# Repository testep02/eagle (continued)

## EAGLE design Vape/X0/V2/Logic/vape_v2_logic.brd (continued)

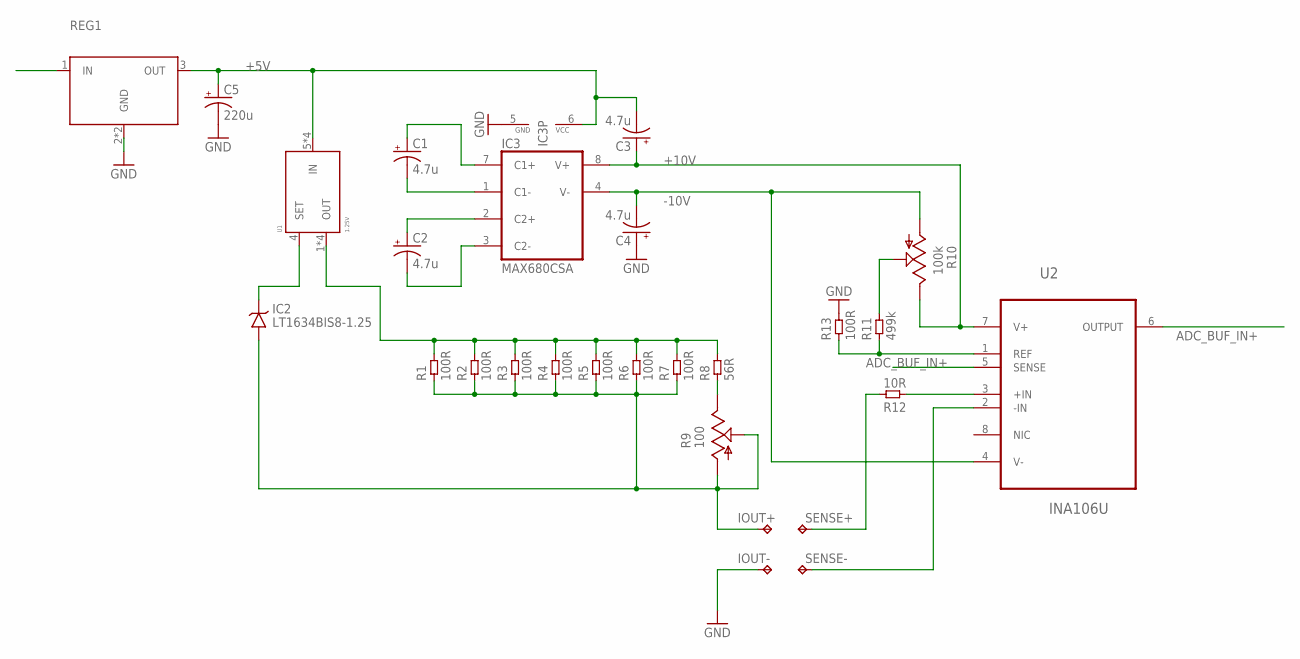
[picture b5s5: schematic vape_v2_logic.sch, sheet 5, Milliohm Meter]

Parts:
C1, C2, C3, C4: 4.7u; B/3528-21R; PART# T521B475M035ATE150
C5: 220u; PANASONIC_C
IC2: LT1634BIS8-1.25; S8
IC3: MAX680CSA; SO08
IOUT+: TPPAD1-17; P1-17
IOUT-: TPPAD1-17; P1-17
R1, R2, R3, R4, R5, R6, R7: 100R; 0603L3; PART# APC0603T100RZ
R8: 56R; 0603L3; PART# APC0603T100RZ
R9: 100; 3223W
R10: 100k; 3223W
R11: 499k; 0603L3
R12: 10R; 0603L3
R13: 100R; 0603L3
REG1: LDO_REG_4PIN; SOT-223-3
SENSE+: TPPAD1-17; P1-17
SENSE-: TPPAD1-17; P1-17
U1: 1.25V; DD-8
U2: INA106U; SOIC127P600X175-8N

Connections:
+5V: C3.-, C5.+, IC3.6 (VCC), REG1.3 (OUT), U1.5 (IN), U1.6 (IN), U1.7 (IN), U1.8 (IN)
+10V: C3.+, IC3.8 (V+), R10.3 (E), U2.7 (V+)
-10V: C4.-, IC3.4 (V-), R10.1 (A), U2.4 (V-)
ADC_BUF_IN+: U2.5 (SENSE), U2.6 (OUTPUT); also elsewhere on the board
CC: IC2.4 (GND), IOUT+.TP, R1.P$1 (1), R2.P$1 (1), R3.P$1 (1), R4.P$1 (1), R5.P$1 (1), R6.P$1 (1), R7.P$1 (1), R9.1 (A), R9.2 (S)
CC_OUT: R1.P$2 (2), R2.P$2 (2), R3.P$2 (2), R4.P$2 (2), R5.P$2 (2), R6.P$2 (2), R7.P$2 (2), R8.P$2 (2), U1.1 (OUT), U1.2 (OUT), U1.3 (OUT), U1.9 (OUT)
GND: C4.+, C5.-, IC3.5 (GND), IOUT-.TP, R13.P$2 (2), REG1.2 (GND), REG1.4 (GND); also elsewhere on the board
MEAS_NEG: SENSE-.TP, U2.2 (-IN)
MEAS_POS: R12.P$2 (2), SENSE+.TP
unnamed: IC2.6 (VOUT), U1.4 (SET)
unnamed: C1.-, IC3.1 (C1-)
unnamed: C2.+, IC3.2 (C2+)
unnamed: C1.+, IC3.7 (C1+)
unnamed: C2.-, IC3.3 (C2-)
unnamed: R12.P$1 (1), U2.3 (+IN)
unnamed: R8.P$1 (1), R9.3 (E)
unnamed: R11.P$1 (1), R13.P$1 (1), U2.1 (REF)
unnamed: R10.2 (S), R11.P$2 (2)
V_IN: REG1.1 (IN)

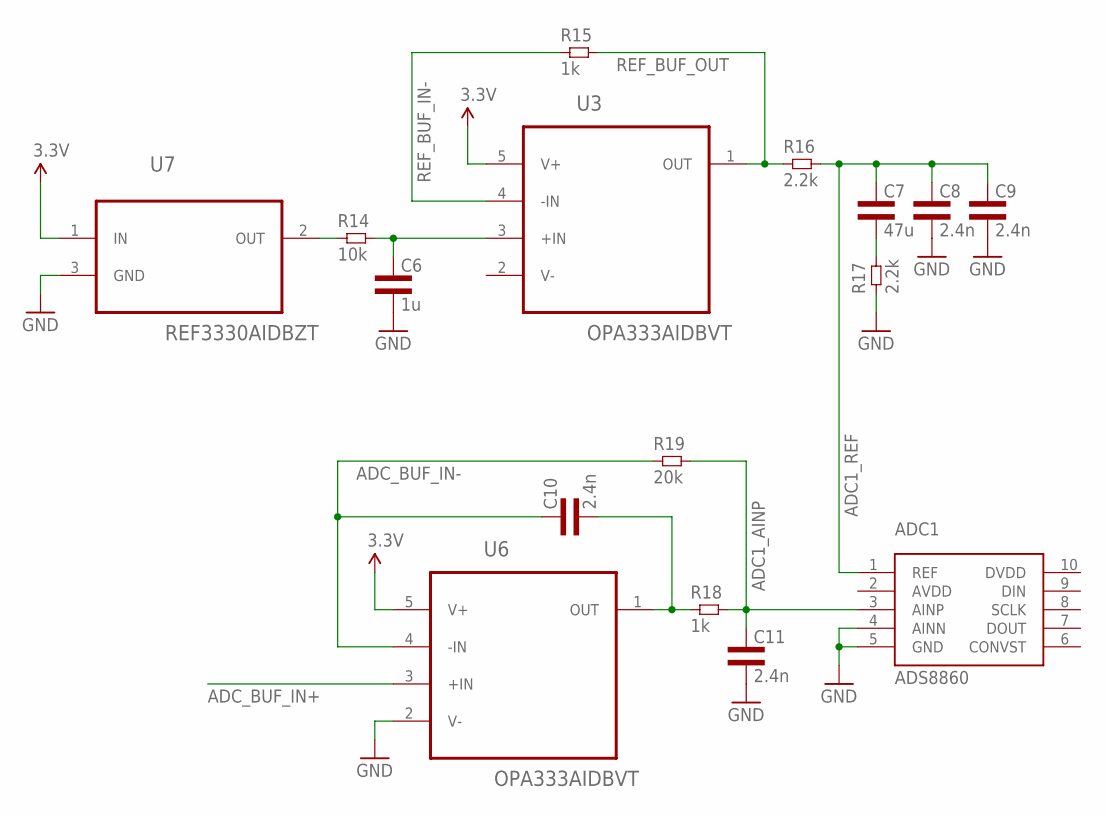
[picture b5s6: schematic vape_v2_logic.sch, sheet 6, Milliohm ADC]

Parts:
ADC1: ADS8860IDGSR; S-PDSO-G10
C6: 1u; 0603L3
C7: 47u; 0805L3; PART# C2012JB1A476M125AC
C8, C9, C10, C11: 2.4n; 0603L3
R14: 10k; 0603L3
R15, R18: 1k; 0603L3
R16, R17: 2.2k; 0603L3
R19: 20k; 0603L3
U3, U6: OPA333AIDBVT; SOT95P280X145-5N
U7: REF3330AIDBZT; SOT95P237X112-3N

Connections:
3.3V: U3.5 (V+), U6.5 (V+), U7.1 (IN); also elsewhere on the board
ADC1_AINP: ADC1.3 (AINP), C11.P$1 (1), R18.P$2 (2), R19.P$2 (2)
ADC1_REF: ADC1.1 (REF), C7.1, C8.P$1 (1), C9.P$1 (1), R16.P$2 (2)
ADC_BUF_IN+: U6.3 (+IN); also elsewhere on the board
ADC_BUF_IN-: C10.P$1 (1), R19.P$1 (1), U6.4 (-IN)
ADC_BUF_OUT: C10.P$2 (2), R18.P$1 (1), U6.1 (OUT)
GND: ADC1.4 (AINN), ADC1.5 (GND), C6.P$2 (2), C8.P$2 (2), C9.P$2 (2), C11.P$2 (2), R17.P$1 (1), U6.2 (V-), U7.3 (GND); also elsewhere on the board
unnamed: C7.2, R17.P$2 (2)
REF_BUF_IN+: C6.P$1 (1), R14.P$2 (2), U3.3 (+IN)
REF_BUF_IN-: R15.P$1 (1), U3.4 (-IN)
REF_BUF_OUT: R15.P$2 (2), R16.P$1 (1), U3.1 (OUT)
REF_OUT: R14.P$1 (1), U7.2 (OUT)
V-: U3.2 (V-)

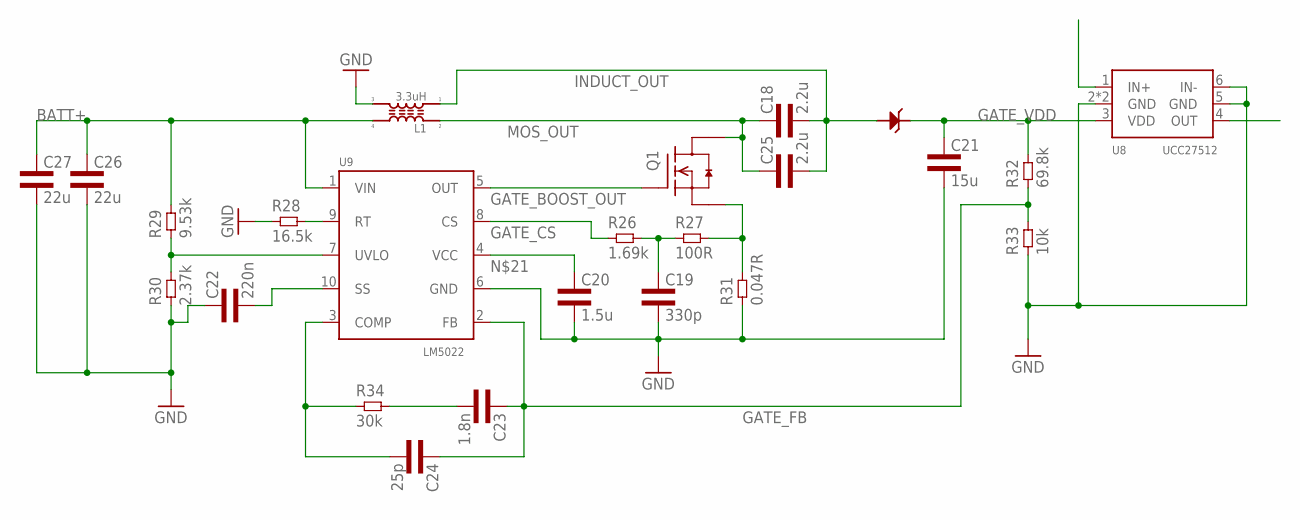
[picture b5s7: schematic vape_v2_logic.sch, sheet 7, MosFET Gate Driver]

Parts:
C18, C25: 2.2u; 0402L3
C19: 330p; 0402L3
C20: 1.5u; 0402L3
C21: 15u; 1206L3
C22: 220n; 0402L3
C23: 1.8n; 0402L3
C24: 25p; 0402L3
C26, C27: 22u; 1206L3
D1: .77V / 5.5A; DPAK
L1: 3.3uH; DRQ12X
Q1: OPEN-BLDC_FDMC7664; OPEN-BLDC_MLP33
R26: 1.69k; 0402L3
R27: 100R; 0402L3
R28: 16.5k; 0402L3
R29: 9.53k; 0402L3
R30: 2.37k; 0402L3
R31: 0.047R; 1206L3
R32: 69.8k; 0402L3
R33: 10k; 0402L3
R34: 30k; 0402L3
U8: UCC27512; S-PWSON-N6
U9: LM5022; S-PDSO-G10

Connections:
BATT+: C26.1, C27.1, L1.4, R29.P$2 (2), U9.1 (VIN); also elsewhere on the board
GATE_BOOST_OUT: Q1.4G (G), U9.5 (OUT)
GATE_COMP: C24.P$2 (2), R34.P$1 (1), U9.3 (COMP)
GATE_CS: R26.P$1 (1), U9.8 (CS)
GATE_FB: C23.P$1 (1), C24.P$1 (1), R32.P$1 (1), R33.P$2 (2), U9.2 (FB)
GATE_SS: C22.P$2 (2), U9.10 (SS)
GATE_UVLO: R29.P$1 (1), R30.P$2 (2), U9.7 (UVLO)
GATE_VDD: C21.1, D1.TAB (CATHODE), R32.P$2 (2), U8.3 (VDD)
GND: C19.P$2 (2), C20.P$2 (2), C21.2, C22.P$1 (1), C26.2, C27.2, L1.3, R28.P$1 (1), R30.P$1 (1), R31.1, R33.P$1 (1), U8.2 (GND), U8.5 (GND), U8.6 (IN-), U8.TP (GND), U9.6 (GND); also elsewhere on the board
INDUCT_OUT: C18.P$2 (2), C25.P$2 (2), D1.1 (ANODE), D1.3 (ANODE), L1.1
MOS_OUT: C18.P$1 (1), C25.P$1 (1), L1.2, Q1.5678D (D)
unnamed: C19.P$1 (1), R26.P$2 (2), R27.P$1 (1)
unnamed: Q1.123S (S), R27.P$2 (2), R31.2
unnamed: C20.P$1 (1), U9.4 (VCC)
unnamed: R28.P$2 (2), U9.9 (RT)
unnamed: C23.P$2 (2), R34.P$2 (2)

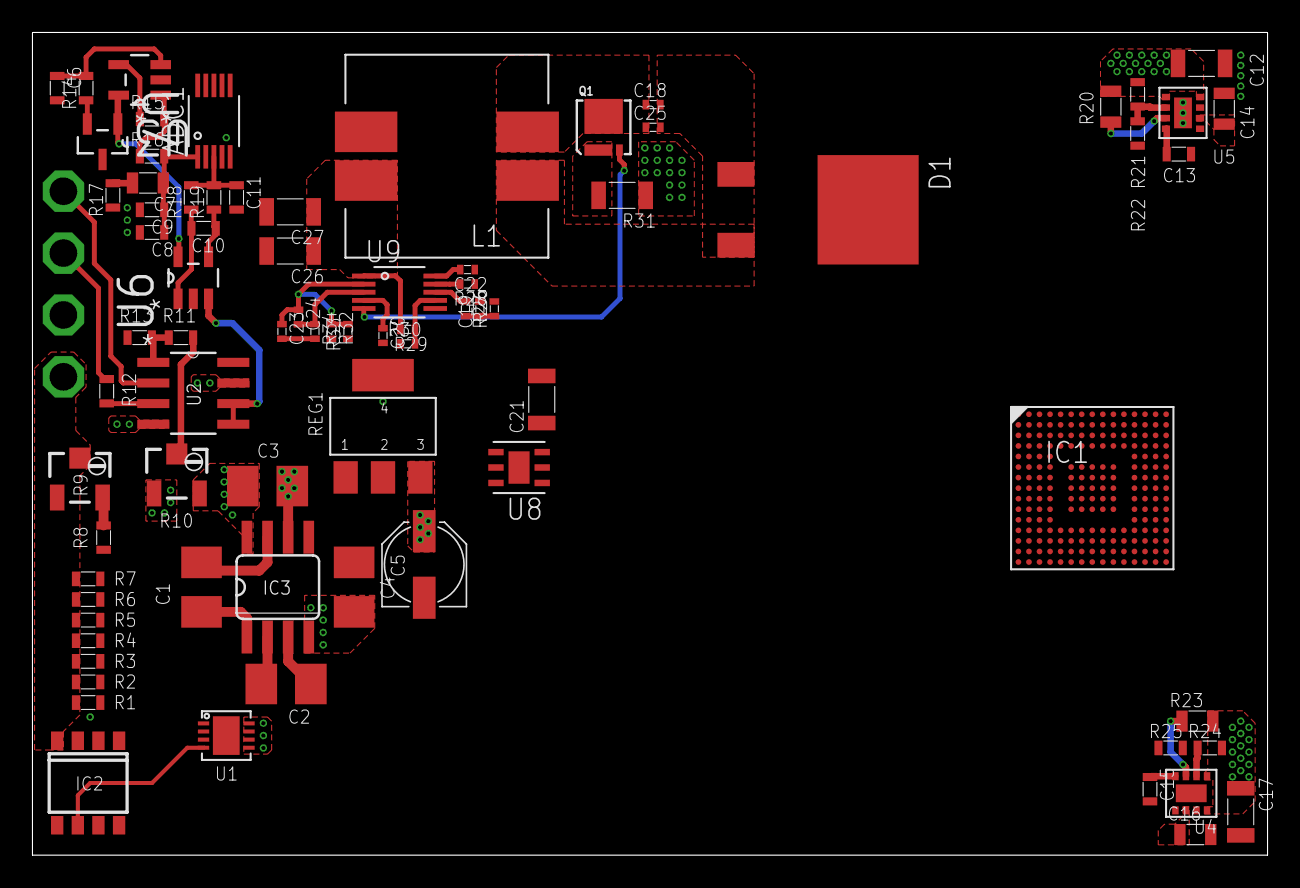
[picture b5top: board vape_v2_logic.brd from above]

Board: 4 copper layers, 76.1 x 50.7 mm, 82 parts (0 on the bottom side), 50 nets.

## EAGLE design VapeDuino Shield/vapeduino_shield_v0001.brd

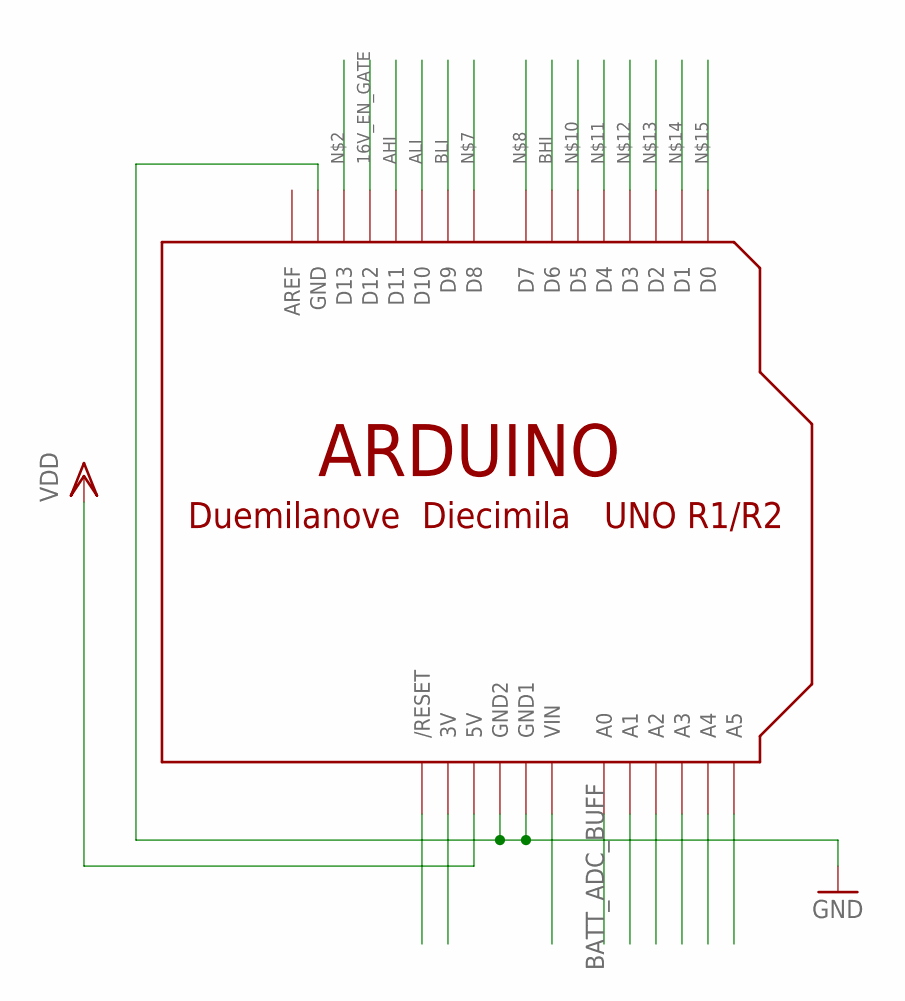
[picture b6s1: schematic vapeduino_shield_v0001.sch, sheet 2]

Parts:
U$1: ARDUINOUNO; ARDUINO

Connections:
16V_EN_GATE: U$1.D12; also elsewhere on the board
AHI: U$1.D11; also elsewhere on the board
ALI: U$1.D10; also elsewhere on the board
BATT_ADC_BUFF: U$1.A0; also elsewhere on the board
BHI: U$1.D6; also elsewhere on the board
BLI: U$1.D9; also elsewhere on the board
COIL_RES_ADC: U$1.A1; also elsewhere on the board
GND: U$1.GND, U$1.GND1, U$1.GND2; also elsewhere on the board
VDD: U$1.5V; also elsewhere on the board

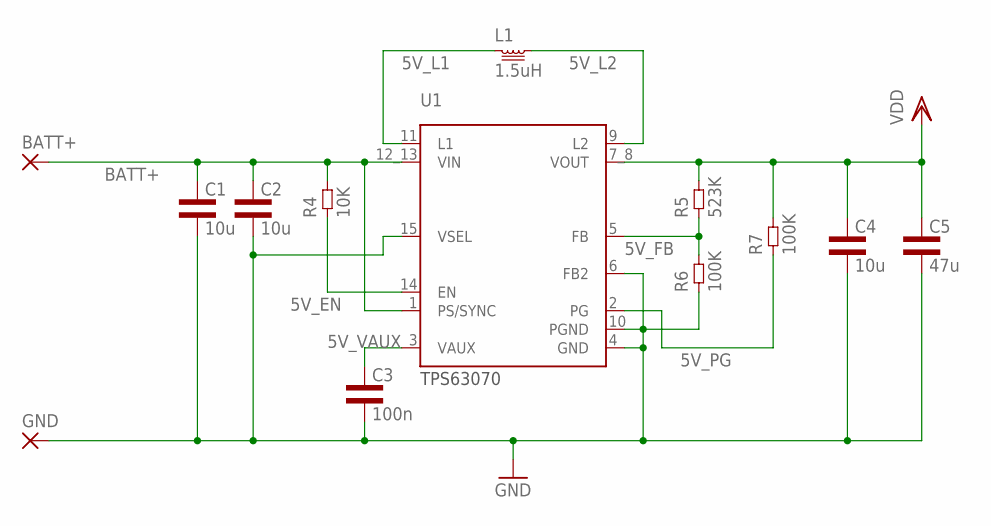
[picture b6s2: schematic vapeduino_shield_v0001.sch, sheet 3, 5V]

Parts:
BATT+: SMD5; SMD2,54-5,08
C1, C2, C4: 10u; 0603L3
C3: 100n; 0603L3
C5: 47u; 0805L3
GND: SMD5; SMD2,54-5,08
L1: 1.5uH; 4X4
R4: 10K; 0603L3
R5: 523K; 0603L3
R6, R7: 100K; 0603L3
U1: TPS63070; VQFN-HR

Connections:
5V_EN: R4.P$1 (1), U1.14 (EN)
5V_FB: R5.P$1 (1), R6.P$2 (2), U1.5 (FB)
5V_L1: L1.1, U1.11 (L1)
5V_L2: L1.2, U1.9 (L2)
5V_PG: R7.P$1 (1), U1.2 (PG)
5V_VAUX: C3.P$1 (1), U1.3 (VAUX)
BATT+: BATT+.1, C1.P$1 (1), C2.P$1 (1), R4.P$2 (2), U1.1 (PS/SYNC), U1.12_13 (VIN); also elsewhere on the board
GND: C1.P$2 (2), C2.P$2 (2), C3.P$2 (2), C4.P$2 (2), C5.2, GND.1, R6.P$1 (1), U1.4 (GND), U1.6 (FB2), U1.10 (PGND), U1.15 (VSEL); also elsewhere on the board
VDD: C4.P$1 (1), C5.1, R5.P$2 (2), R7.P$2 (2), U1.7_8 (VOUT); also elsewhere on the board

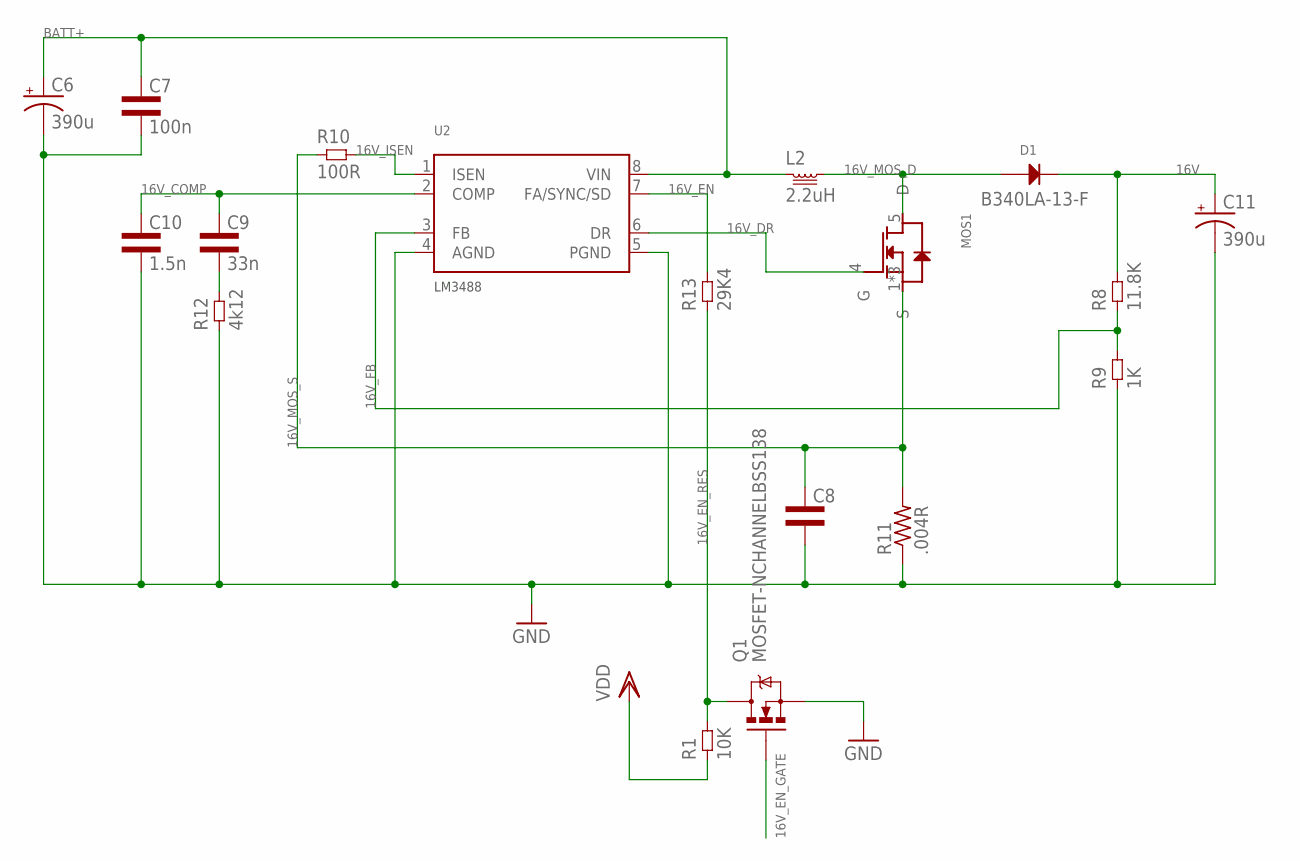
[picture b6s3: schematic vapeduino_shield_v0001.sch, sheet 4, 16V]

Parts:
C6, C11: 390u; PANASONIC_G
C7: 100n; 0603L3
C8: CAP0603L3; 0603L3
C9: 33n; 0402L3
C10: 1.5n; 0402L3
D1: DIODESMA; SMA; PART# B340LA-13-F
L2: 2.2uH; 7.7X8
MOS1: MOSFET-NQ3; Q3
Q1: MOSFET-NCHANNELBSS138; SOT23
R1: 10K; 0603L3
R8: 11.8K; 0603L3
R9: 1K; 0603L3
R10: 100R; 0603L3
R11: .004R; R2512
R12: 4k12; 0402L3
R13: 29K4; 0603L3
U2: LM3488; S-PDSO-G8

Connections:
16V: C11.+, D1.2 (CATHODE), R8.P$2 (2); also elsewhere on the board
16V_COMP: C9.P$1 (1), C10.P$1 (1), U2.2 (COMP)
16V_DR: MOS1.4 (G), U2.6 (DR)
16V_EN: R13.P$2 (2), U2.7 (FA/SYNC/SD)
16V_EN_GATE: Q1.1 (G); also elsewhere on the board
16V_EN_RES: Q1.3 (D), R1.P$2 (2), R13.P$1 (1)
16V_FB: R8.P$1 (1), R9.P$2 (2), U2.3 (FB)
16V_ISEN: R10.P$2 (2), U2.1 (ISEN)
16V_MOS_D: D1.1 (ANODE), L2.2, MOS1.5 (D)
16V_MOS_S: C8.P$1 (1), MOS1.1 (S), MOS1.2 (S), MOS1.3 (S), R10.P$1 (1), R11.2
BATT+: C6.+, C7.P$1 (1), L2.1, U2.8 (VIN); also elsewhere on the board
GND: C6.-, C7.P$2 (2), C8.P$2 (2), C10.P$2 (2), C11.-, Q1.2 (S), R9.P$1 (1), R11.1, R12.P$1 (1), U2.4 (AGND), U2.5 (PGND); also elsewhere on the board
unnamed: C9.P$2 (2), R12.P$2 (2)
VDD: R1.P$1 (1); also elsewhere on the board

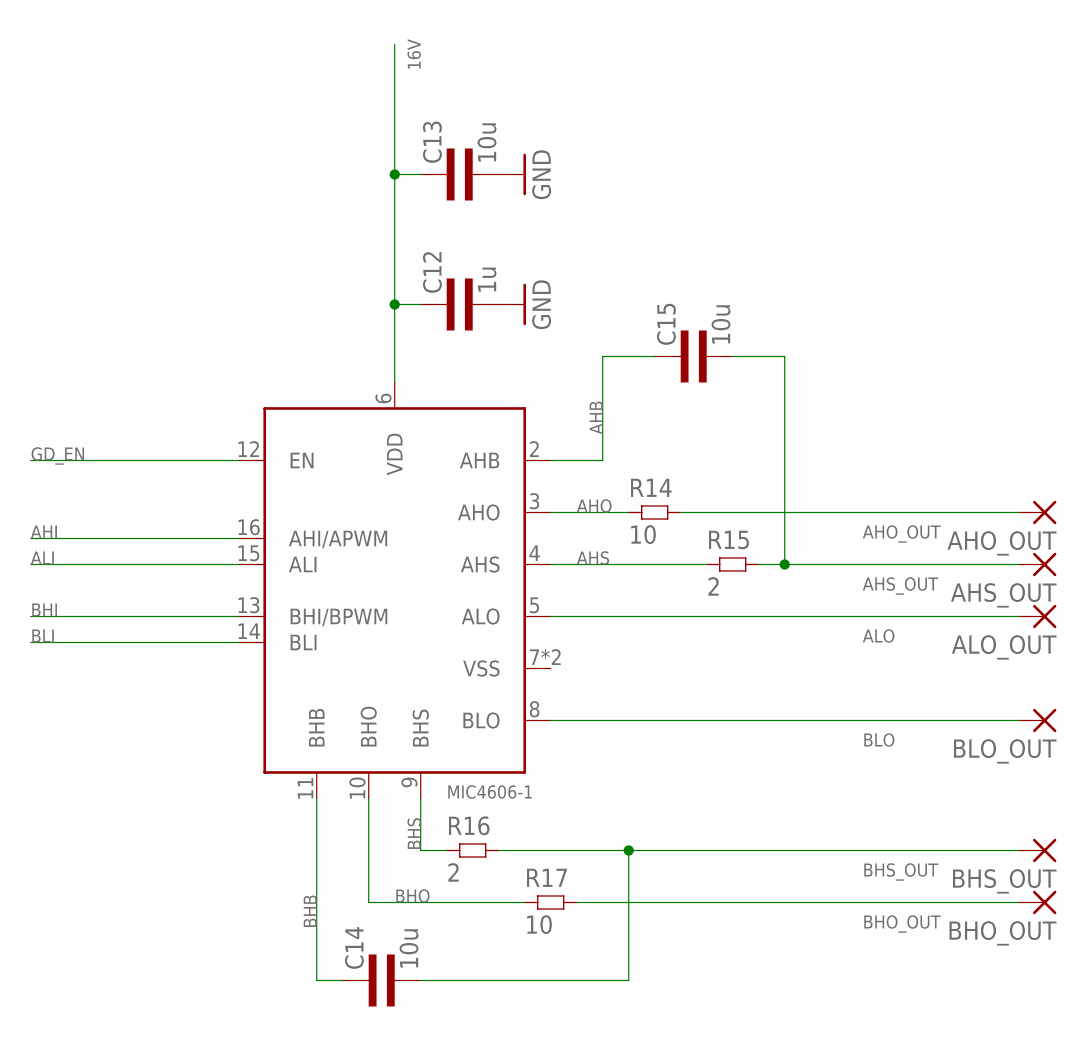
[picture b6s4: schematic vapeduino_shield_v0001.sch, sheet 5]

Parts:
AHO_OUT: 3,17/1,3
AHS_OUT: 3,17/1,3
ALO_OUT: 3,17/1,3
BHO_OUT: 3,17/1,3
BHS_OUT: 3,17/1,3
BLO_OUT: 3,17/1,3
C12: 1u; 0603L3
C13: 10u; 0805L3
C14, C15: 10u; 1206L3
MD1: MIC4606-1; QFN44-16LD-PL-2
R14, R17: 10; 0805L3
R15, R16: 2; 0805L3

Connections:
16V: C12.P$1 (1), C13.1, MD1.6 (VDD); also elsewhere on the board
AHB: C15.1, MD1.2 (AHB)
AHI: MD1.16 (AHI/APWM); also elsewhere on the board
AHO: MD1.3 (AHO), R14.1
AHO_OUT: AHO_OUT.1, R14.2
AHS: MD1.4 (AHS), R15.1
AHS_OUT: AHS_OUT.1, C15.2, R15.2; also elsewhere on the board
ALI: MD1.15 (ALI); also elsewhere on the board
ALO: ALO_OUT.1, MD1.5 (ALO)
BHB: C14.1, MD1.11 (BHB)
BHI: MD1.13 (BHI/BPWM); also elsewhere on the board
BHO: MD1.10 (BHO), R17.1
BHO_OUT: BHO_OUT.1, R17.2
BHS: MD1.9 (BHS), R16.1
BHS_OUT: BHS_OUT.1, C14.2, R16.2
BLI: MD1.14 (BLI); also elsewhere on the board
BLO: BLO_OUT.1, MD1.8 (BLO)
GD_EN: MD1.12 (EN)
GND: C12.P$2 (2), C13.2; also elsewhere on the board

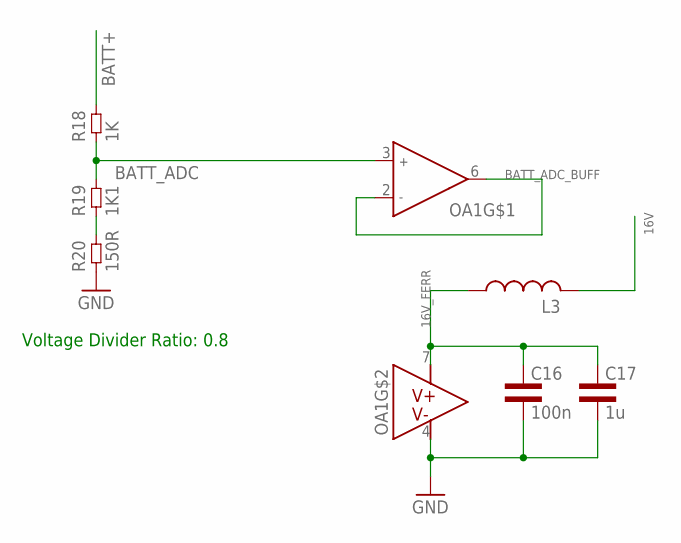
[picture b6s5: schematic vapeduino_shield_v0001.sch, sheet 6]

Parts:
C16: 100n; 0603L3
C17: 1u; 0805L3
L3: L-USL1812; L1812
OA1: OPA659DRB; S-PVSON-N8
R18: 1K; 0603L3
R19: 1K1; 0603L3
R20: 150R; 0603L3

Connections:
16V: L3.2; also elsewhere on the board
16V_FERR: C16.P$1 (1), C17.1, L3.1, OA1.7 (V+)
BATT+: R18.P$2 (2); also elsewhere on the board
BATT_ADC: OA1.3 (INA+), R18.P$1 (1), R19.P$2 (2)
BATT_ADC_BUFF: OA1.2 (INA-), OA1.6 (OUTA); also elsewhere on the board
GND: C16.P$2 (2), C17.2, OA1.4 (V-), R20.P$1 (1); also elsewhere on the board
unnamed: R19.P$1 (1), R20.P$2 (2)

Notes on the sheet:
Voltage Divider Ratio: 0.8

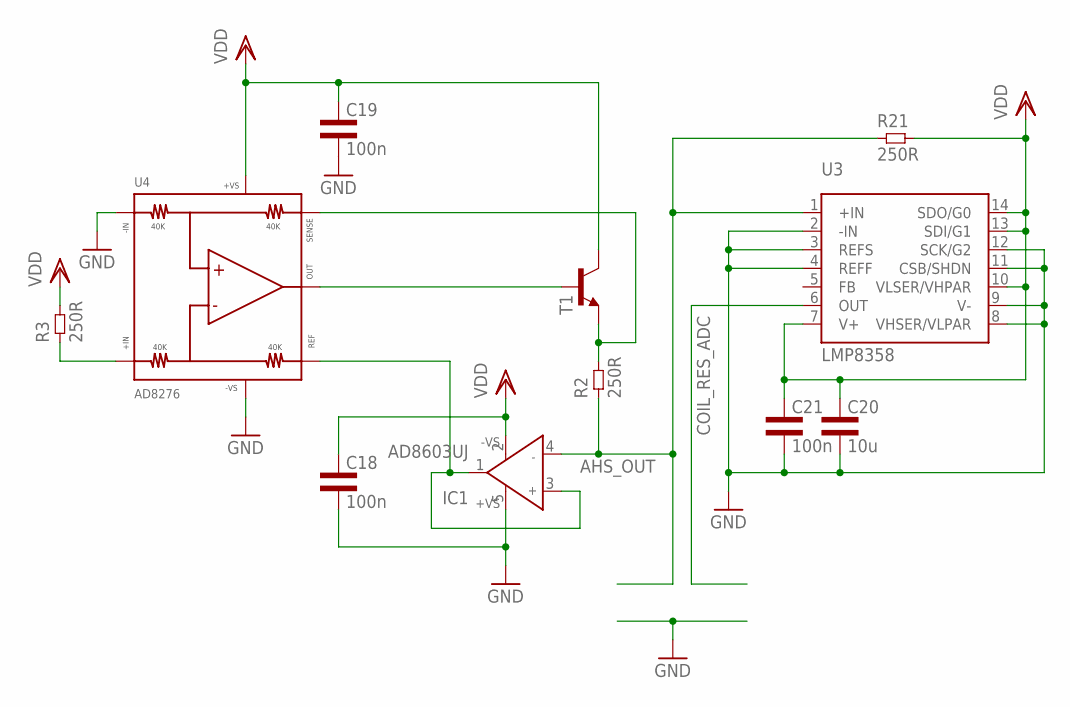
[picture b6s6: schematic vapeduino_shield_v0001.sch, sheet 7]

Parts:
C18, C19, C21: 100n; 0603L3
C20: 10u; 0805L3
IC1: AD8603UJ; SOT23-5
R2, R3, R21: 250R; 0603L3
T1: TRANSISTOR_MMBT3904LT1-NPN-SOT23-BEC; TRANSISTOR_SOT23-BEC
U3: LMP8358; R-PDSO-G14
U4: AD8276BRMZ; S-PDSO-G8

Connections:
AHS_OUT: IC1.4 (IN-), R2.P$1 (1), R21.P$1 (1), U3.1 (+IN); also elsewhere on the board
COIL_RES_ADC: U3.6 (OUT); also elsewhere on the board
GND: C18.P$2 (2), C19.P$2 (2), C20.2, C21.P$2 (2), IC1.5 (+VS), U3.2 (-IN), U3.3 (REFS), U3.4 (REFF), U3.8 (VHSER/VLPAR), U3.9 (V-), U3.11 (CSB/SHDN), U3.12 (SCK/G2), U4.2 (-IN), U4.4 (-VS); also elsewhere on the board
unnamed: T1.B, U4.6 (OUT)
unnamed: R2.P$2 (2), T1.E, U4.5 (SENSE)
unnamed: IC1.1 (OUT), IC1.3 (IN+), U4.1 (REF)
unnamed: R3.P$1 (1), U4.3 (+IN)
VDD: C18.P$1 (1), C19.P$1 (1), C20.1, C21.P$1 (1), IC1.2 (-VS), R3.P$2 (2), R21.P$2 (2), T1.C, U3.7 (V+), U3.10 (VLSER/VHPAR), U3.13 (SDI/G1), U3.14 (SDO/G0), U4.7 (+VS); also elsewhere on the board

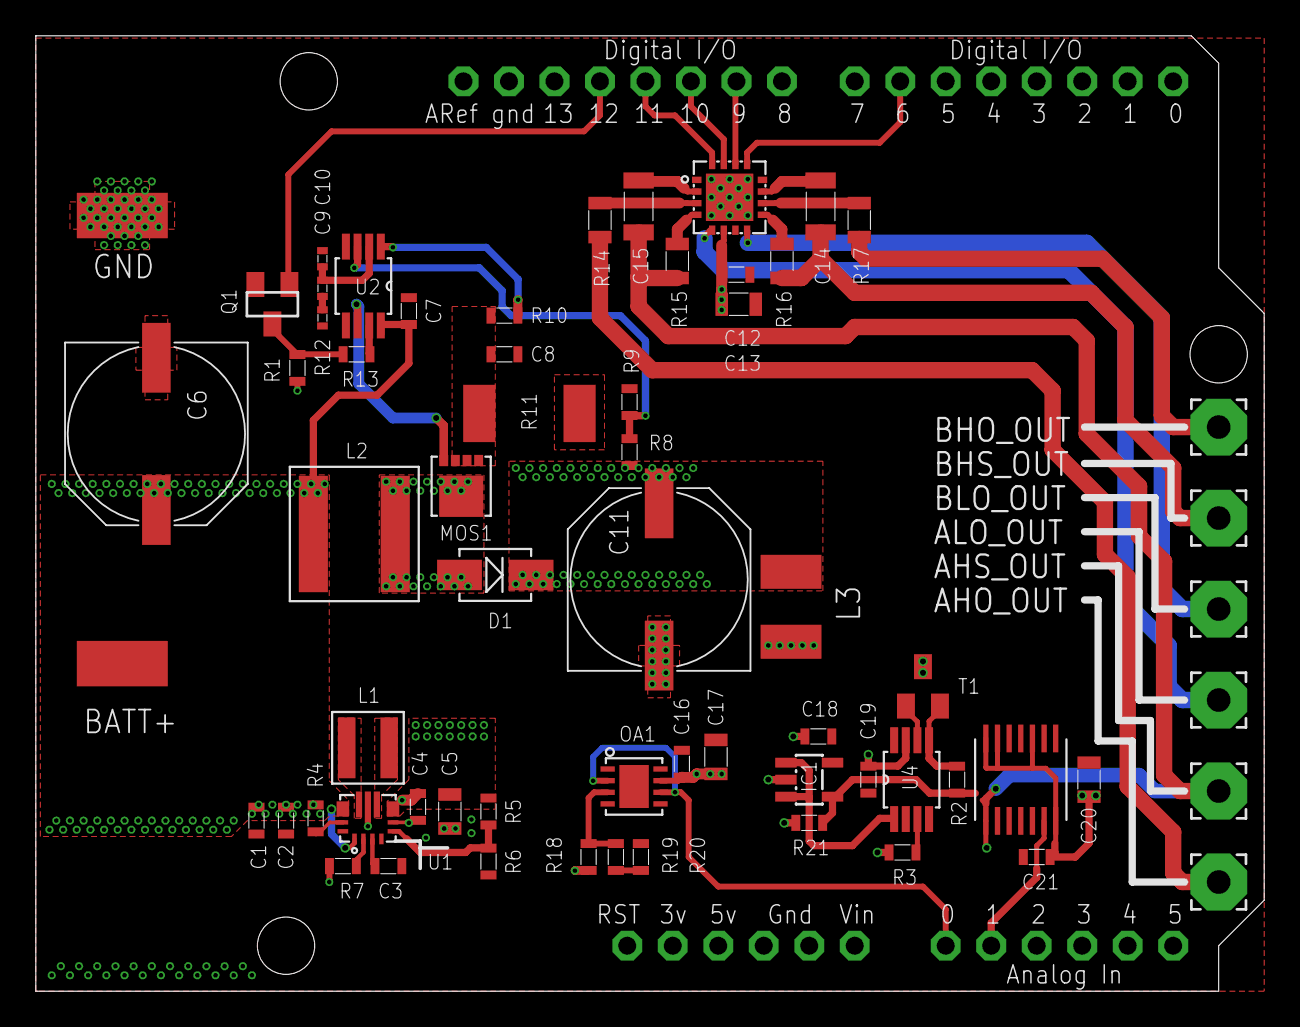
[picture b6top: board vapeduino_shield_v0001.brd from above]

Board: 4 copper layers, 68.6 x 53.3 mm, 65 parts (0 on the bottom side), 45 nets.

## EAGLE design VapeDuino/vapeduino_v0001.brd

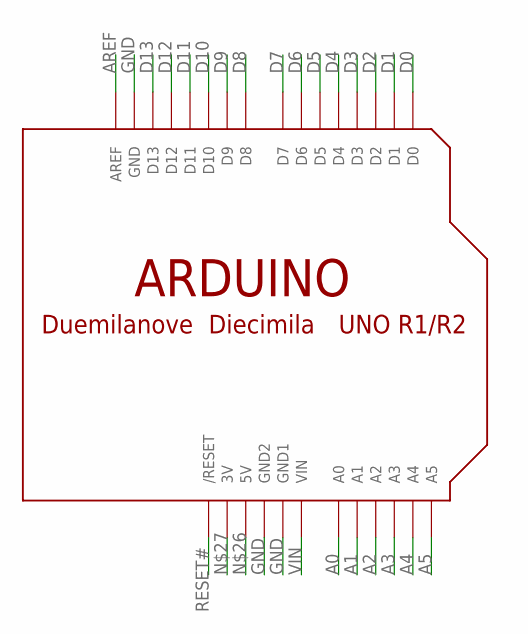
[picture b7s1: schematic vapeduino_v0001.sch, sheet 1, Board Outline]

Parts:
U$1: ARDUINOUNO; ARDUINO

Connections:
A0: U$1.A0
A1: U$1.A1
A2: U$1.A2
A3: U$1.A3
A4: U$1.A4
A5: U$1.A5
AREF: U$1.AREF
D0: U$1.D0
D1: U$1.D1
D2: U$1.D2
D3: U$1.D3
D4: U$1.D4
D5: U$1.D5
D6: U$1.D6
D7: U$1.D7
D8: U$1.D8
D9: U$1.D9
D10: U$1.D10
D11: U$1.D11
D12: U$1.D12
D13: U$1.D13
GND: U$1.GND, U$1.GND1, U$1.GND2; also elsewhere on the board
RESET#: U$1.RESET (/RESET)
VIN: U$1.VIN

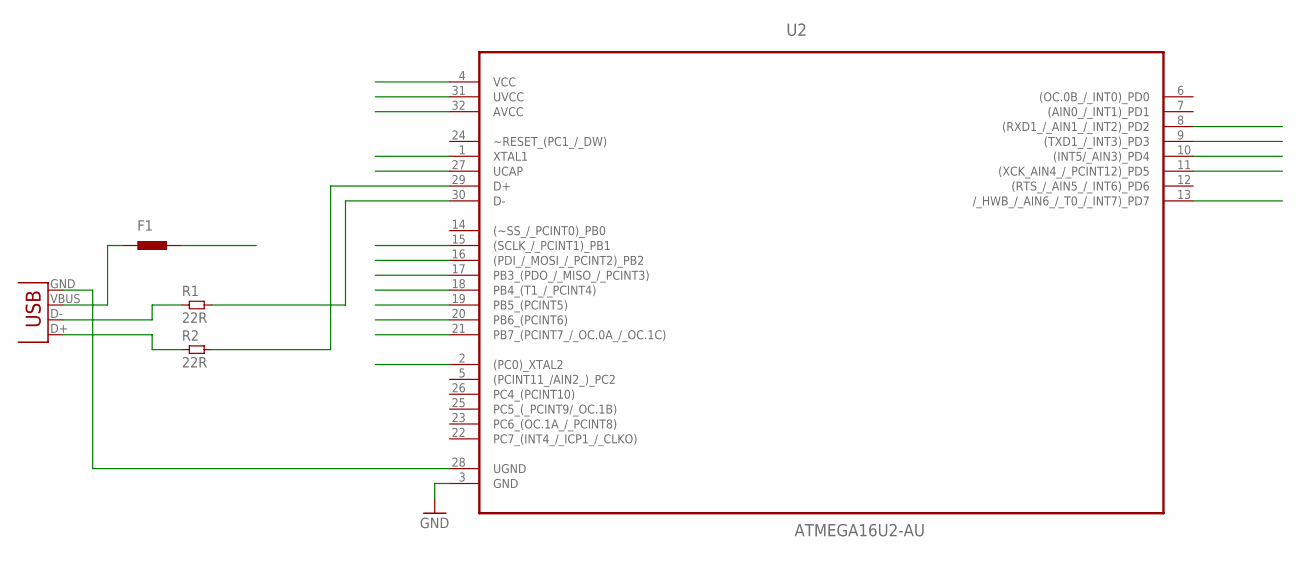
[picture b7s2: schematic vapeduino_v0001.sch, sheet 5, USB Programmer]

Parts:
F1: RES_FUSE; 1812
JP2: USB-B; USB-B-PTH
R1, R2: 22R; 0603L3
U2: ATMEGA16U2-AU; QFP80P900X900X120-32N

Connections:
GND: U2.3 (GND); also elsewhere on the board
unnamed: JP2.D-, R1.P$1 (1)
unnamed: JP2.D+, R2.P$1 (1)
unnamed: R2.P$2 (2), U2.29 (D+)
unnamed: R1.P$2 (2), U2.30 (D-)
unnamed: JP2.GND, U2.28 (UGND)
unnamed: F1.1, JP2.VBUS

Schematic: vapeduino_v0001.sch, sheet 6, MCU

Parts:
U1: ATMEGA328; QFN32

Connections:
GND: U1.P$3 (GND), U1.P$5 (GND), U1.P$21 (GND); also elsewhere on the board

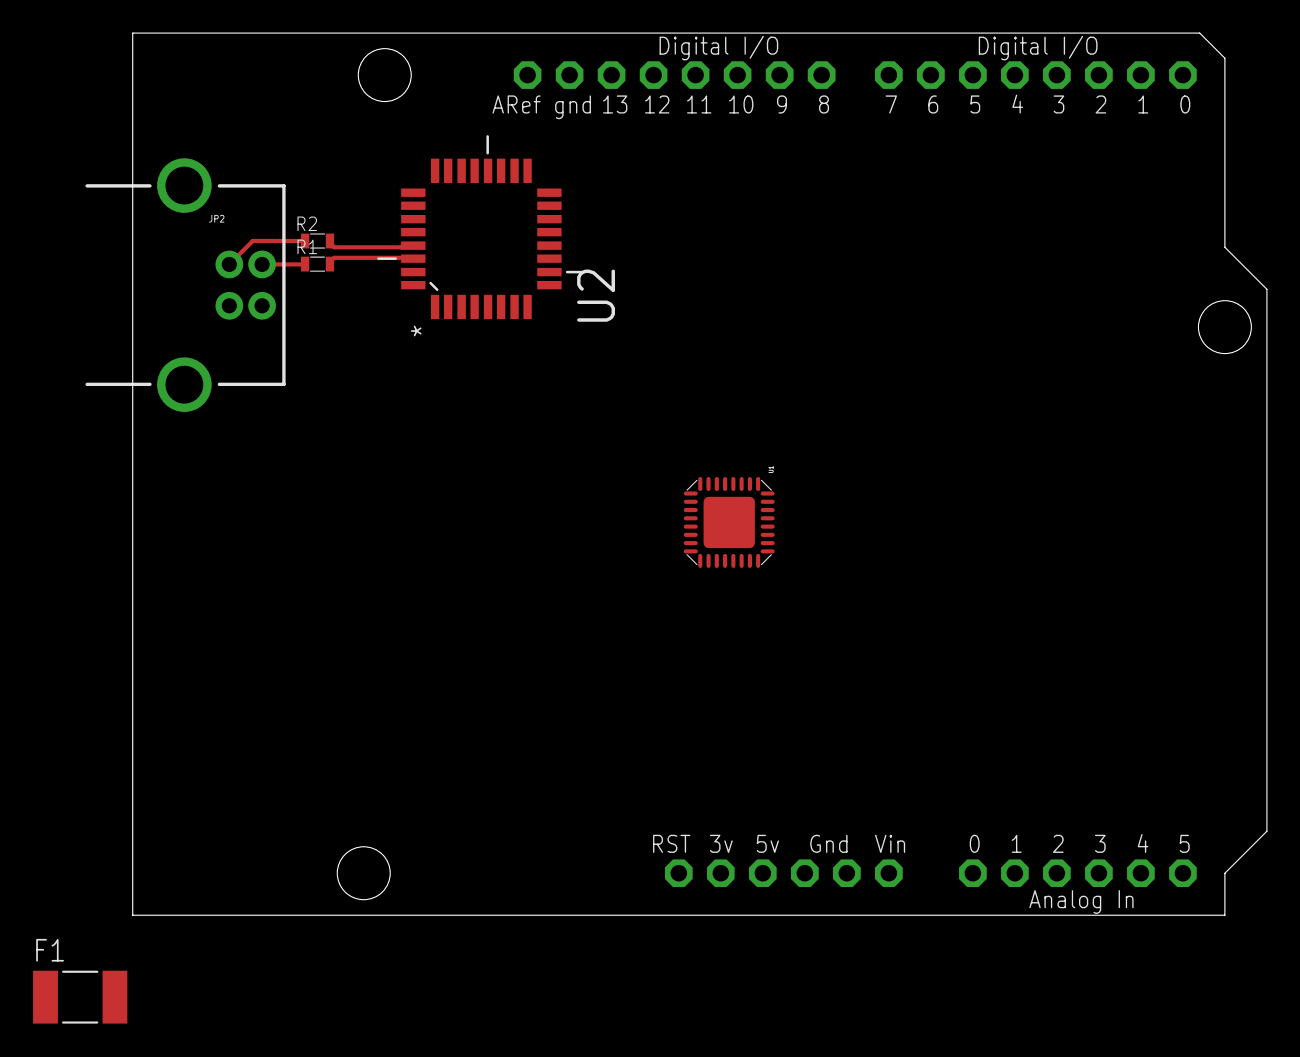
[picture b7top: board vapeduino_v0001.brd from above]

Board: 2 copper layers, 68.6 x 53.3 mm, 7 parts (0 on the bottom side), 7 nets.
